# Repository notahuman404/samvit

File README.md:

# Samvit 👁️🌉

> *Samvit (संवित्) — Sanskrit for "Conscious Awareness"*

> **"We don't just navigate the system for blind users — we navigate the world."**

An AI-powered assistive system that helps visually impaired individuals independently find, understand, and physically reach public services — starting with healthcare.

---

## 🧩 The Problem

Visually impaired individuals face **two walls**, not one:

1. They can't independently navigate apps or screens to find nearby healthcare, benefits, or public services
2. Even when someone helps them find it — **they still can't get there alone**

Existing solutions solve neither problem completely. Screen readers tell you *what's on screen* but don't help you *understand* or *act*. Navigation apps help sighted people. Nothing bridges both worlds.

---

## 💡 The Solution

Samvit is a **two-layer assistive system** combining AI software and sensory hardware:

### 🧠 Layer 1 — Software (The Brain)
A Jarvis-like voice AI that understands your phone screen and the web on your behalf.

- Say *"Find me the nearest free clinic"* — it searches, reads, filters, and explains results in plain language
- Guides users through benefits eligibility questions conversationally
- Makes phone calls on command (*"Call the clinic and ask if they take walk-ins"*)
- Reads and interprets any screen content aloud with context, not just raw text

### 👁️ Layer 2 — Hardware (The Game-Changer)
A wearable sensory substitution device inspired by Neil Harbisson's pioneering work in human sensory extension.

- Uses **heatmapping** to translate the visual environment into sensory feedback
- Converts spatial information (obstacles, paths, destinations) into perceivable signals
- Allows the user to **physically navigate** to their destination — independently, without a guide
- Works in real-time alongside the software layer for end-to-end assistance

---

## 🎯 Challenge Alignment

**Brief 4 — Public Service, Direction A: Benefits Navigator**

| Requirement | Samvit |
|---|---|
| Help users interpret rules and reduce confusion | ✅ Voice AI simplifies eligibility criteria in plain language |
| Translate criteria into plain language | ✅ Reads and contextualizes screen content aloud |
| Ask questions to guide users through their situation | ✅ Conversational AI walks users step by step |
| Healthcare as a primary use case | ✅ Core use case of the product |
| Go beyond a directory — help users actually act | ✅ Hardware ensures they can physically reach the service |

---

## 🏗️ Architecture Overview

```
User Voice Input
      │
      ▼
┌─────────────────────┐
│   Voice AI Layer    │  ← Understands intent, reads screen, navigates web
│  (Jarvis Engine)    │
└────────┬────────────┘
         │
         ▼
┌─────────────────────┐
│  Screen & Web       │  ← Finds clinics, reads eligibility, makes calls
│  Understanding      │
└────────┬────────────┘
         │
         ▼
┌─────────────────────┐
│  Hardware Layer     │  ← Heatmap-based sensory substitution wearable
│  (Sensory Bridge)   │    guides user to physical destination
└─────────────────────┘
```

---

## 🔬 Inspiration

- **Neil Harbisson** — Pioneer of sensory substitution; the first human officially recognized as a cyborg, who perceives color through sound via his "eyeborg" antenna
- **Sensory Substitution Research** — The science of routing one sense's information through another (e.g., visual data → tactile or auditory feedback)
- **Heatmap Navigation** — Using thermal/spatial density mapping to encode environmental information into perceivable signals

---

## 🔩 Hardware Validation & Testing

Our hardware pipeline — from depth sensing through motor actuation — has been validated through a **datasheet-driven simulation** that goes well beyond simple mocking. Rather than stubbing out I2C calls and calling it tested, we built physically-accurate models of every component in the signal chain and ran them against the actual firmware logic.

### What we validated

| Component | Validation Method |
|---|---|
| Intel RealSense D435i depth cameras | Noise model fitted to Intel's published accuracy data: quadratic noise growth (σ = 2mm at 1m, 8mm at 2m, 32mm at 4m), distance-dependent dropout rates, edge artifacts, flying pixel simulation |
| NXP PCA9685 motor drivers (×9) | Full I2C protocol verification against datasheet Rev.4: init sequence timing, register payload format, ALLCALL broadcast, 65-byte raw writes (bypassing SMBus 32-byte cap) |
| Dual-camera depth fusion | Min-distance overlap logic with statistically-verified output across 100+ noisy frames. Invalid readings (0) never corrupt fusion — verified with 50,000 samples |
| 144-motor grid (12×12) | Bijective channel mapping (144 → 9 boards × 16 channels), single-motor precision addressing, rapid on/off cycling stability |
| I2C bus (BCM2711 BSC, 400kHz) | Timing budget calculated from first principles (9 clocks/byte × 400kHz), bus utilization analysis, clock stretching model |

### Fault injection (not just happy-path)

The simulation injects real hardware failures and verifies graceful degradation:

- **Board failure isolation** — one PCA9685 dies, the other 8 continue operating (128/144 motors still active)
- **Brown-out detection** — supply drops below 2.7V, bus operations halt safely before corrupting registers
- **Stuck I2C bus** — SCL held low (common with loose connections), detected and reported within one transaction attempt
- **Bus contention (NACK storms)** — 5% random NACK rate with retry logic achieves 100% frame delivery
- **Thermal performance** — I2C transactions validated at 70°C operating temperature with oscillator drift model

### Stress testing

- **1,000 continuous frames** with dynamically moving obstacles — zero errors, 0.28ms avg loop time (99.4% headroom on 50ms budget)
- **500 rapid on/off cycles** — verifies register write stability under worst-case duty cycling
- **Bug regression suite** — 3 previously-identified firmware bugs verified fixed (SMBus cap #11, ALLCALL bit #12, invalid-depth mapping #13)

### How to run

```bash
cd hardware/tests
python hil_simulation.py --verbose
```

Outputs a structured JSON report (`hil_results.json`) suitable for CI integration, with per-test metrics, timing data, and pass/fail status.

---

## 🚀 MVP Scope

**Phase 1 — Software MVP**
- [x] Voice-activated screen reader with contextual understanding
- [x] Healthcare clinic finder with eligibility pre-screening
- [x] Conversational benefits guidance flow
- [x] One-tap call routing to clinics/services
- [x] Agentic flow: multi-step goal execution with voice control

**Phase 2 — Hardware Prototype**
- [x] Wearable sensor unit (C++ firmware, ARM-compiled)
- [x] Heatmap generation from dual depth cameras
- [x] Sensory feedback output (144 vibration motors, 12×12 grid)
- [x] Integration with software navigation layer
- [x] Hardware validation suite (22 tests, datasheet-verified)

---

## 👥 Target Users

- Visually impaired individuals (partial or full vision loss)
- Blind individuals navigating public services independently
- Families assisting visually impaired members remotely
- Community organizations supporting disability access

---

## 🌍 Impact

Every other Benefits Navigator is just an app. Samvit goes further:

- **Finds** the nearest relevant service
- **Explains** eligibility in plain language
- **Calls** on your behalf
- **Gets you there** — physically, independently

This isn't just accessibility software. It's **independence as a service.**

---

## 🛠️ Running Locally

### Prerequisites

- [Android Studio](https://developer.android.com/studio) (Ladybug or newer recommended)
- Python 3.10+ (for backend)
- A [Gemini API key](https://aistudio.google.com/apikey) (free tier works)
- A `google-services.json` from your GenAI project (for GenAI AI SDK)

### Step 1 — Clone the repo

```bash
git clone https://github.com/mrehan0516/Vision_Guide.git
cd Vision_Guide
```

### Step 2 — Set up the Gemini API key

Create a `.env` file in the project root (same level as `settings.gradle.kts`):

```bash
cp .env.example .env
```

Edit `.env` and replace the placeholder with your real key:

```
GEMINI_API_KEY=your_actual_gemini_api_key_here
```

This key is used by both the Android app (via the Secrets Gradle Plugin) and the Python backend.

### Step 3 — GenAI setup

Place your `google-services.json` file in the `app/` directory. You can get this from your [GenAI Console](https://console.firebase.google.com/) → Project Settings → General → Your Apps → Download `google-services.json`.

### Step 4 — Run the Android app

1. Open Android Studio
2. Select **Open** and choose the `Vision_Guide` directory
3. Let Gradle sync complete (it will download all dependencies automatically)
4. If you see a signing config error, remove this line from `app/build.gradle.kts`:
   ```
   signingConfig = signingConfigs.getByName("debugConfig")
   ```
5. Connect a physical Android device (recommended — accessibility features work best on real devices) or start an emulator
6. Click **Run** (green play button) or press `Shift+F10`

> **Note:** The app uses a `MockVisionPilotClient` by default, so it works without the backend running. The mock simulates the full agent plan → step → confirm flow for demo purposes.

### Step 5 — Run the backend (optional, for full Gemini-powered agent)

```bash
cd backend
pip install fastapi uvicorn google-generativeai pydantic
```

Set the API key in your terminal:

```bash
export GEMINI_API_KEY=your_actual_gemini_api_key_here
```

Start the server:

```bash
python main.py
```

The backend runs on `http://localhost:8000`. API docs are available at `http://localhost:8000/docs`.

### Step 6 — Run the hardware simulation (no hardware needed)

```bash
cd hardware/tests
python hil_simulation.py --verbose
```

This runs the full 22-test HIL validation suite and outputs results to `hil_results.json`.

### Quick reference — what runs where

| Component | How to run | Needs hardware? |
|---|---|---|
| Android app (mock mode) | Android Studio → Run | No (phone or emulator) |
| Android app (live agent) | Android Studio → Run + backend on | No (phone + laptop) |
| Backend API | `python main.py` | No |
| Hardware simulation | `python hil_simulation.py` | No |
| Haptic vest firmware | `./haptic_vest` (on RPi4) | Yes (RPi4 + cameras + motors) |

---

## 🙏 Credits & Acknowledgments

### AI Tools Used in Development

| Tool | Role | Tier |
|---|---|---|
| **Google Gemini 2.0 Flash** | Core AI backbone — powers the agentic reasoning engine, screen understanding, multimodal vision (screenshot OCR), goal decomposition, and step planning | Free tier |
| **Devin** (by Cognition AI) | AI software engineer — built the C++ firmware port, HIL simulation suite, agentic backend (`agent.py`), and Android integration | Free tier |
| **Claude** (by Anthropic) | AI assistant — helped with architecture planning, code review, and documentation | Free tier |

### Open-Source Libraries & Frameworks

**Android App:**
| Library | Purpose |
|---|---|
| [Jetpack Compose](https://developer.android.com/jetpack/compose) | Declarative UI framework |
| [GenAI AI](https://firebase.google.com/docs/vertex-ai) | Gemini model access via GenAI |
| [Retrofit](https://square.github.io/retrofit/) + [OkHttp](https://square.github.io/okhttp/) | HTTP client for backend communication |
| [Moshi](https://github.com/square/moshi) | JSON serialization |
| [CameraX](https://developer.android.com/training/camerax) | Camera capture pipeline |
| [Kotlin Coroutines](https://kotlinlang.org/docs/coroutines-overview.html) | Async/concurrent programming |
| [Accompanist Permissions](https://google.github.io/accompanist/permissions/) | Runtime permission handling |
| [Room](https://developer.android.com/training/data-storage/room) | Local database |
| [Navigation Compose](https://developer.android.com/jetpack/compose/navigation) | In-app navigation |

**Backend (Python):**
| Library | Purpose |
|---|---|
| [FastAPI](https://fastapi.tiangolo.com/) | REST API framework |
| [google-generativeai](https://github.com/google-gemini/generative-ai-python) | Gemini API client |
| [Pydantic](https://docs.pydantic.dev/) | Data validation & serialization |
| [Uvicorn](https://www.uvicorn.org/) | ASGI server |

**Hardware Firmware (C++):**
| Library | Purpose |
|---|---|
| [Intel RealSense SDK (librealsense2)](https://github.com/IntelRealSense/librealsense) | Dual D435i depth camera capture |
| [CMake](https://cmake.org/) | Cross-platform build system |
| C++ Standard Library (`std::thread`, `std::mutex`) | Threading & synchronization |
| Linux I2C (`i2c-dev`, `I2C_RDWR` ioctl) | Raw I2C communication with PCA9685 boards |

**Hardware Components:**
| Component | Spec |
|---|---|
| Raspberry Pi 4B | Cortex-A72, BCM2711, I2C Fast Mode (400kHz) |
| Intel RealSense D435i (×2) | Stereo depth cameras, 640×480 @ 30fps |
| NXP PCA9685 (×9) | 16-channel 12-bit PWM drivers |
| ERM Vibration Motors (×144) | 12×12 haptic grid, 3V/75mA each |

### Methodology Note

The hardware simulation (`hardware/tests/hil_simulation.py`) uses noise models and timing parameters derived from published datasheets — not arbitrary mock values. All protocol sequences were validated against NXP PCA9685 Datasheet Rev.4 (2015) and Intel RealSense D435i specifications (2019).

---

## 📄 License

MIT License — Open for contribution and community development.

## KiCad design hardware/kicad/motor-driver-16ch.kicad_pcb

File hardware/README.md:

# Haptic Feedback Vest — Hardware Design

144-channel vibrotactile vest driven by a Raspberry Pi 4, two Intel RealSense D435i depth cameras, and nine PCA9685 PWM controllers switching AO3400A MOSFETs into Precision Microdrives 310-113 ERM coin motors.

## Directory Layout

```
hardware/
├── README.md                       ← this file
├── bom/
│   ├── bom-master.csv              ← full consolidated BOM
│   └── bom-notes.md                ← sourcing notes, substitutions, tolerances
├── schematics/
│   ├── top-level-block-diagram.md  ← system block diagram (ASCII)
│   ├── motor-driver-cell.md        ← single MOSFET driver cell (repeat ×144)
│   ├── pca9685-chain.md            ← I2C chain and addressing
│   ├── power-tree.md               ← full power distribution tree
│   └── raspberry-pi-pinout.md      ← Pi GPIO assignments
├── assembly/
│   ├── assembly-guide.md           ← step-by-step build sequence
│   ├── motor-grid-layout.md        ← 12×12 grid, numbering, spacing
│   └── connector-plan.md           ← JST, FFC, USB connector specs
├── firmware-notes/
│   ├── motor-addressing.md         ← PCA9685 → motor index mapping
│   └── latency-budget.md           ← pipeline timing to hit <50 ms
└── tests/
    └── validation-procedures.md    ← hardware smoke tests and validation
```

## Quick-Start Summary

| Item | Value |
|---|---|
| Haptic channels | 144 |
| Motor grid | 12 × 12 |
| PWM controllers | 9 × PCA9685 (I2C) |
| MOSFET switches | 144 × AO3400A |
| Depth sensors | 2 × Intel RealSense D435i (USB 3) |
| Compute | Raspberry Pi 4 4 GB |
| Audio amp | MAX98357A (I2S) |
| Motor supply | 3 V rail |
| Logic supply | 5 V rail |
| Estimated peak draw | ~31 W |
| Estimated average draw | ~16 W |
| Target power bank | 65 W USB-C PD, ≥ 20 000 mAh |
| Target end-to-end latency | < 50 ms |

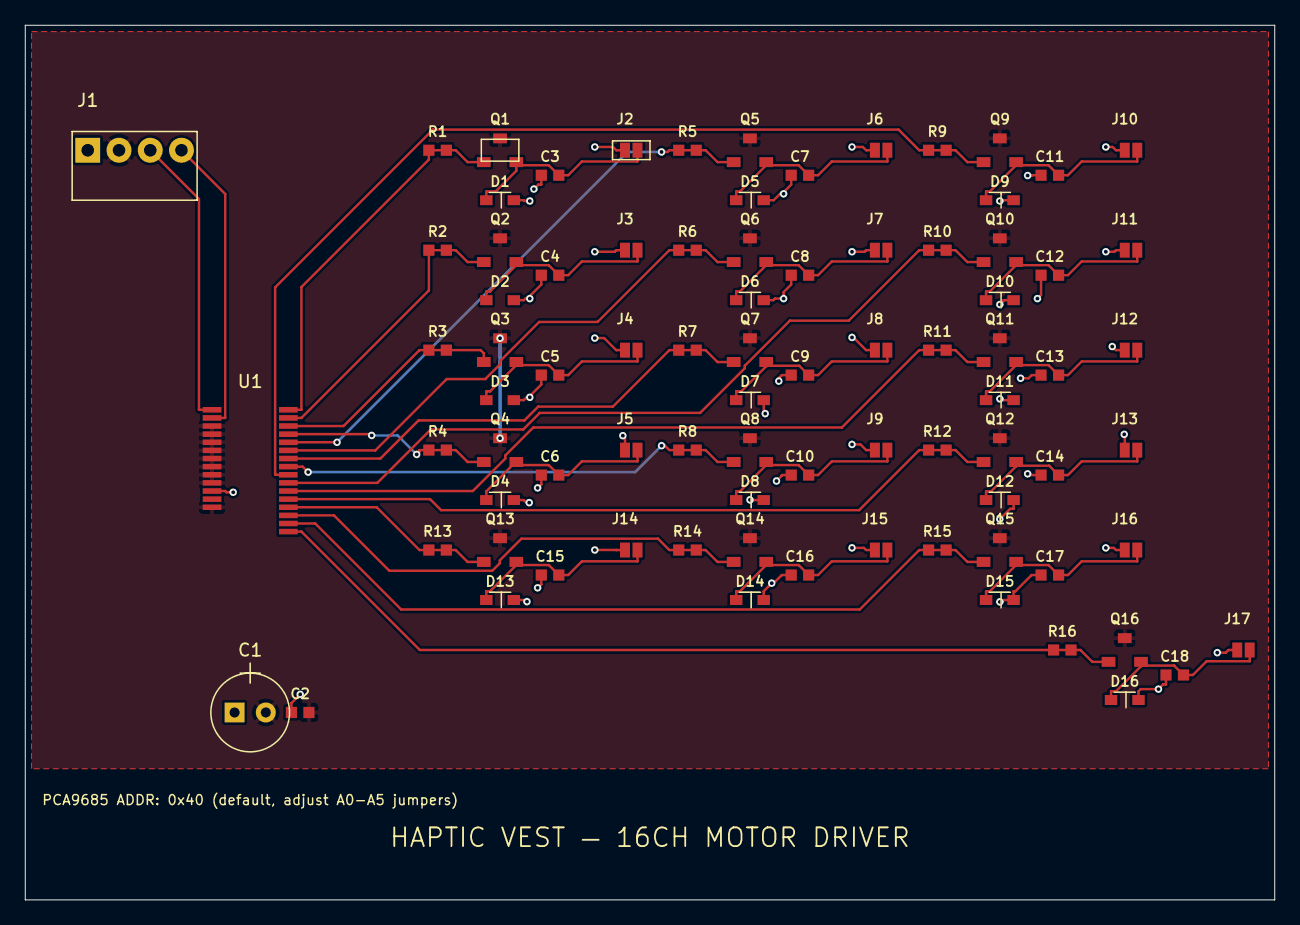
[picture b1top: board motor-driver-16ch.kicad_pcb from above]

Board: 2 copper layers, 100.0 x 70.0 mm, 84 parts (0 on the bottom side), 37 nets.

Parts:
C1: 100uF 16V; CP_Radial_D6.3mm_P2.50mm
C2, C3, C4, C5, C6, C7, C8, C9, C10, C11, C12, C13, C14, C15, C16, C17, C18: 100nF; C_0402_1005Metric
D1, D2, D3, D4, D5, D6, D7, D8, D9, D10, D11, D12, D13, D14, D15, D16: 1N4148WS; D_SOD-323
J1: I2C_PWR_IN; JST_XH_B4B-XH-A_1x04_P2.50mm_Vertical
J2: M001; JST_SH_SM02B-SRSS-TB_1x02-1MP_P1.00mm_Horizontal
J3: M002; JST_SH_SM02B-SRSS-TB_1x02-1MP_P1.00mm_Horizontal
J4: M003; JST_SH_SM02B-SRSS-TB_1x02-1MP_P1.00mm_Horizontal
J5: M004; JST_SH_SM02B-SRSS-TB_1x02-1MP_P1.00mm_Horizontal
J6: M005; JST_SH_SM02B-SRSS-TB_1x02-1MP_P1.00mm_Horizontal
J7: M006; JST_SH_SM02B-SRSS-TB_1x02-1MP_P1.00mm_Horizontal
J8: M007; JST_SH_SM02B-SRSS-TB_1x02-1MP_P1.00mm_Horizontal
J9: M008; JST_SH_SM02B-SRSS-TB_1x02-1MP_P1.00mm_Horizontal
J10: M009; JST_SH_SM02B-SRSS-TB_1x02-1MP_P1.00mm_Horizontal
J11: M010; JST_SH_SM02B-SRSS-TB_1x02-1MP_P1.00mm_Horizontal
J12: M011; JST_SH_SM02B-SRSS-TB_1x02-1MP_P1.00mm_Horizontal
J13: M012; JST_SH_SM02B-SRSS-TB_1x02-1MP_P1.00mm_Horizontal
J14: M013; JST_SH_SM02B-SRSS-TB_1x02-1MP_P1.00mm_Horizontal
J15: M014; JST_SH_SM02B-SRSS-TB_1x02-1MP_P1.00mm_Horizontal
J16: M015; JST_SH_SM02B-SRSS-TB_1x02-1MP_P1.00mm_Horizontal
J17: M016; JST_SH_SM02B-SRSS-TB_1x02-1MP_P1.00mm_Horizontal
Q1, Q2, Q3, Q4, Q5, Q6, Q7, Q8, Q9, Q10, Q11, Q12, Q13, Q14, Q15, Q16: AO3400A; SOT-23
R1, R2, R3, R4, R5, R6, R7, R8, R9, R10, R11, R12, R13, R14, R15, R16: 220R; R_0402_1005Metric
U1: PCA9685; TSSOP-28_4.4x9.7mm_P0.65mm

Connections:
+3V: C3.1, C4.1, C5.1, C6.1, C7.1, C8.1, C9.1, C10.1, C11.1, C12.1, C13.1, C14.1, C15.1, C16.1, C17.1, C18.1, D1.K, D2.K, D3.K, D4.K, D5.K, D6.K, D7.K, D8.K, D9.K, D10.K, D11.K, D12.K, D13.K, D14.K, D15.K, D16.K, J2.1, J3.1, J4.1, J5.1, J6.1, J7.1, J8.1, J9.1, J10.1, J11.1, J12.1, J13.1, J14.1, J15.1, J16.1, J17.1
+5V: C1.1, C2.1, J1.1, U1.25
DRAIN_CH00: C3.2, D1.A, J2.2, Q1.2
DRAIN_CH01: C4.2, D2.A, J3.2, Q2.2
DRAIN_CH02: C5.2, D3.A, J4.2, Q3.2
DRAIN_CH03: C6.2, D4.A, J5.2, Q4.2
DRAIN_CH04: C7.2, D5.A, J6.2, Q5.2
DRAIN_CH05: C8.2, D6.A, J7.2, Q6.2
DRAIN_CH06: C9.2, D7.A, J8.2, Q7.2
DRAIN_CH07: C10.2, D8.A, J9.2, Q8.2
DRAIN_CH08: C11.2, D9.A, J10.2, Q9.2
DRAIN_CH09: C12.2, D10.A, J11.2, Q10.2
DRAIN_CH10: C13.2, D11.A, J12.2, Q11.2
DRAIN_CH11: C14.2, D12.A, J13.2, Q12.2
DRAIN_CH12: C15.2, D13.A, J14.2, Q13.2
DRAIN_CH13: C16.2, D14.A, J15.2, Q14.2
DRAIN_CH14: C17.2, D15.A, J16.2, Q15.2
DRAIN_CH15: C18.2, D16.A, J17.2, Q16.2
GND: C1.2, C2.2, J1.2, Q1.3, Q2.3, Q3.3, Q4.3, Q5.3, Q6.3, Q7.3, Q8.3, Q9.3, Q10.3, Q11.3, Q12.3, Q13.3, Q14.3, Q15.3, Q16.3, U1.3, U1.4, U1.5, U1.6, U1.7, U1.8, U1.19, U1.24, U1.28
PWM_CH00: Q1.1, R1.1, R1.2, U1.9
PWM_CH01: Q2.1, R2.1, R2.2, U1.10
PWM_CH02: Q3.1, R3.1, R3.2, U1.11
PWM_CH03: Q4.1, R4.1, R4.2, U1.12
PWM_CH04: Q5.1, R5.1, R5.2, U1.13
PWM_CH05: Q6.1, R6.1, R6.2, U1.14
PWM_CH06: Q7.1, R7.1, R7.2, U1.15
PWM_CH07: Q8.1, R8.1, R8.2, U1.16
PWM_CH08: Q9.1, R9.1, R9.2, U1.17
PWM_CH09: Q10.1, R10.1, R10.2, U1.18
PWM_CH10: Q11.1, R11.1, R11.2, U1.20
PWM_CH11: Q12.1, R12.1, R12.2, U1.21
PWM_CH12: Q13.1, R13.1, R13.2, U1.22
PWM_CH13: Q14.1, R14.1, R14.2, U1.23
PWM_CH14: Q15.1, R15.1, R15.2, U1.27
PWM_CH15: Q16.1, R16.1, R16.2, U1.29
SCL: J1.4, U1.2
SDA: J1.3, U1.1

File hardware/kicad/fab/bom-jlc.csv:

Comment,Designator,Footprint,LCSC Part #,Manufacturer,MPN,Qty,Unit Price USD (est.),Description
PCA9685PW,U1,Package_SO:TSSOP-28_4.4x9.7mm_P0.65mm,C9067,NXP,PCA9685PW,1,1.50,16-channel 12-bit I2C PWM/Servo controller TSSOP-28
AO3400A,"Q1,Q2,Q3,Q4,Q5,Q6,Q7,Q8,Q9,Q10,Q11,Q12,Q13,Q14,Q15,Q16",Package_TO_SOT_SMD:SOT-23,C20917,AOS,AO3400A,16,0.08,30V 4A N-Channel MOSFET Vgs(th)max=1.45V SOT-23
220R,"R1,R2,R3,R4,R5,R6,R7,R8,R9,R10,R11,R12,R13,R14,R15,R16",Resistor_SMD:R_0402_1005Metric,C25091,Yageo,RC0402FR-07220RL,16,0.01,220 Ohm 1% 1/16W 0402 gate series resistor
1N4148WS,"D1,D2,D3,D4,D5,D6,D7,D8,D9,D10,D11,D12,D13,D14,D15,D16",Diode_SMD:D_SOD-323,C57759,Vishay,1N4148WS-7-F,16,0.02,Fast switching diode 75V 150mA SOD-323 flyback protection
100nF,"C3,C4,C5,C6,C7,C8,C9,C10,C11,C12,C13,C14,C15,C16,C17,C18",Capacitor_SMD:C_0402_1005Metric,C49678,Yageo,CC0402KRX5R9BB104,16,0.01,100nF 50V X5R 0402 local drain bypass capacitor
100nF,C2,Capacitor_SMD:C_0402_1005Metric,C49678,Yageo,CC0402KRX5R9BB104,1,0.01,100nF 50V X5R 0402 PCA9685 VCC bypass

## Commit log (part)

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2026-06-16 added the hardware parser half complete
2026-06-16 Add simulation, test scenario generator, and metrics engine
    p21: physics-inspired simulation (voltage stability, signal integrity,
    power consumption across all test scenarios).
    p22: auto-generates diverse test scenarios (nominal, peak, idle,
    startup inrush, low-battery, outdoor, wearable-specific).
    p23: aggregates all stage results into a unified DesignMetrics snapshot.
2026-06-16 Add KiCad writer, Gerber exporter, JSONL logging, ASCII visualizer, human override
    p26: Generates .kicad_pro / .kicad_sch / .kicad_pcb from DesignState.
    p27: Produces BOM.csv, pick-place.csv, per-layer Gerbers, drill file.
    p28: Appends structured JSONL run journal for audit trail.
    p29: ASCII pipeline status table, metrics dashboard, issue digest.
    p30: human_overrides.json support — force parts, lock rules, inject nets.
2026-06-16 Add CLI entry point and dependency manifest
    main.py: argparse CLI supporting free-text requirements, JSON req file,
    human override file, --demo mode (built-in haptic wearable design),
    configurable iteration limits, and exit code based on ERC/DRC cleanliness.
    requirements.txt: google-generativeai, requests, beautifulsoup4, tqdm.
    Usage:
    python main.py --demo
2026-06-16 Add requirements parser, architecture planner, datasheet batch parser
    p01: Heuristic + structured requirements ingestion with validation.
    p03: Gemini call #1 — subsystem decomposition in one call (voltages,
    currents, interfaces, power budget, ambiguity flagging).
    p05: Gemini call #2 — batched datasheet extraction for all candidate
    parts in a single API call, with confidence scoring.
2026-06-16 feat: wire hardware_parser + hardware_builder into pipeline
    - hardware_parser: add __init__.py, fix all bare imports → relative imports
    so it works as a proper importable package from anywhere in the repo
    - p07: use hardware_builder.component_retrival for primary DB keyword search,
    in-memory scoring as fallback
    - p08: use hardware_builder.part_selection_engine.PartSelectionEngine
    (offline DB + voltage/current/cost scoring); async wrapped for sync call
2026-06-17 fixed preceeding spaces
2026-06-17 fix: treat unrealistic battery life as a validation error to trigger AI repair loop
2026-06-17 fix(p08_part_selection): avoid asyncio.run inside already-running event loop
    asyncio.run() raises RuntimeError when an event loop is already running
    (the orchestrator is async). Run the coroutine in a worker thread instead
    so it gets its own event loop and the coroutine is always awaited.
2026-06-17 fix(models): treat StageStatus.SKIPPED as ok() in StageResult
    p30_human_override returns SKIPPED when no overrides are configured,
    which is a valid non-error outcome. Without this fix it shows as ❌
    even though the stage ran successfully and had nothing to do.
2026-06-17 fix(models): treat StageStatus.SKIPPED as ok() in StageResult
    p30_human_override returns SKIPPED when no overrides are configured.
    This is a valid no-op, not a failure. Without this fix it shows as ❌.
2026-06-17 fix(visualizer): handle float('inf') battery_h in _bar without overflow
    When estimated_battery_h is float('inf'), int(inf * width) raises
    OverflowError. Clamp to full bar and display 'inf' as a string instead.
2026-06-17 fix(reviewer): replace invalid heuristic adjust_value repair for DRC
    The heuristic fallback generated an adjust_value repair targeting
    p13_placement with no 'field' or 'value' in detail, causing it to
    always be silently skipped in _repair_adjust_value.
    Replaced with:
    - reroute_net on p14_routing (always clears traces for re-route)
    - adjust_value on p15_rules with field=min_clearance_mm, value=0.3
2026-06-17 fix(p08): root cause — reads candidates from wrong attribute + category mismatch
    Bug A (ROOT CAUSE OF EVERYTHING): p08 read candidates_data from
    state.stage_data["p07_component_search"] but state.stage_data is always
    None. p07 stores its 5 candidates-per-subsystem in
    state.stage_results["p07_component_search"].data["candidates"].
    With an empty candidates_data, _pick_from_candidates always returns
    None, so selected={} for every subsystem. This caused:
2026-06-17 fix(p07): category expansion used sub.interface, causing wrong parts to rank first
    _search_via_retrival built a keywords list from:
    [sub.name, sub.category, sub.interface]
    and expanded db_categories from ALL of them via CATEGORY_ALIASES.
    This caused "microcontroller" subsystem (interface="I2C/SPI") to include
    "IO Expander" in its search set, because "I2C" in CATEGORY_ALIASES maps
    to ["IO Expander", "Level Shifter"]. MCP23017 (IO Expander) then scored
2026-06-17 fix(p25_repair): ../../.. → ../.. — repair engine searched wrong DB path, adding ghost parts each round → DRC grew +3 per iteration
2026-06-17 fix(p13): use architecture category for zone placement
    Component DB categories (LDO, BT Module, IMU, Flash, ERM Driver) don't
    match _ZONES keys (POWER, COMMS, SENSOR, MEMORY, ACTUATOR). When comp.category
    is used, 6 of 7 components pile into the default (50,50) zone → overlap.
    Build sub_cat_map from state.architecture so each subsystem goes to its
    correct zone (MCU→35,35; POWER→5,55; SENSOR→5,5; etc.).
2026-06-17 fix(p18): architecture fallback when component current_ma=0
    DB stores current as '50mA' strings; float() conversion fails when the
    'mA' suffix is present → all component.current_ma=0 → total_draw_ma=0
    → battery_life=inf → PWR_UNREALISTIC_BATTERY error every run.
    Fallback: use architecture subsystem current_ma estimates instead.
2026-06-17 fix(p18): architecture fallback when component current_ma=0
    DB stores current as '50mA' strings; suffix causes float() parse failure
    → current_ma=0 for all parts → total_draw_ma=0 → battery=inf → error.
    Fallback: use architecture subsystem current_ma estimates instead.
2026-06-23 took the files i created and changed repository
2026-06-23 fix(backend): add CORS middleware and secure credential endpoint
    - Add CORSMiddleware so web-based tooling can reach the backend
    - Fix /agent/memory/credential to accept a JSON body instead of
    query params (credentials in URLs appear in server logs and
    browser history)
2026-06-23 fix(backend): replace global agent singleton with session-keyed instances
    - The module-level agent singleton was not thread-safe: concurrent
    /agent/plan requests clobbered each other's current_plan and
    action_history
    - Replace with a per-session VisionAgent registry keyed by
    X-Session-ID request header
    - /agent/plan now returns the sessionId so clients can pin subsequent
2026-06-23 fix(android): remove deprecated PROCESS_OUTGOING_CALLS; annotate ACCESS_BACKGROUND_LOCATION
    - PROCESS_OUTGOING_CALLS was deprecated in API 29 (Android 10) and has
    no effect on any modern device. Removed. Use CallScreeningService if
    call interception is ever needed.
    - Added inline comment on ACCESS_BACKGROUND_LOCATION warning that the
    Play Store requires a separate declaration form justifying background
    location access before the app can be submitted
2026-06-23 docs: add KNOWN_GAPS.md tracking features described in doc but not yet built
    Covers all gaps identified in the product specification vs codebase audit:
    1. Call Summarization — no recording/STT pipeline
    2. AI Camera Forensics for Hyper Emergency — not wired to emergency path
    3. Continuous GPS location broadcasting — no background service loop
    4. Ambiguity resolution — partially there, needs reliable Gemini prompting
    5. Dashboard access audit trail — no logging implemented
2026-06-23 feat(security): encrypt Room database with SQLCipher at rest
    Gap 2 — encryption at rest:
    - SamvitDatabase now opens via SupportFactory(passphrase) — all data is
    AES-256 encrypted on disk through SQLCipher 4.5.4.
    - Passphrase is a 32-char random string generated on first launch and stored
    in EncryptedSharedPreferences (backed by Android Keystore AES256-GCM).
    It never appears in logs or preferences in plain text.
2026-06-23 feat(voice): persist session transcripts + audit recall + call summary flow
    Gap 5 — session transcript storage:
    - logCommand() result (row ID) is saved as lastCommandId.
    - reply() calls repo.updateCommandResponse(lastCommandId, text) in IO context
    before speaking, so every TTS string is persisted against its command row.
    Gap 3 — voice recall of audit log:
    - RECALL_AUDIT intent handler reads the most recent DASHBOARD_ACCESS entry
2026-06-23 feat(voice): add Porcupine always-on wake-word engine
    Gap 7 — perpetual listening:
    - PorcupineWakeWordEngine runs Picovoice Porcupine 3.0.1 on a daemon thread.
    - AudioRecord reads PCM frames continuously; engine.process() checks each frame.
    - On wake-word detection, calls orchestrator.speech.startListening() to hand
    off to SpeechRecognitionManager for one full command cycle.
    - Pauses frame processing (Thread.sleep) while orchestrator is SPEAKING or
2026-06-23 docs: close gaps 1-9 in KNOWN_GAPS.md; defer sub-3s AI cycle (gap 10)
    Mark gaps 1–9 as CLOSED with a brief summary of each fix.
    Gap 10 (sub-3-second on-device AI cycle) is deferred — requires ML-ops
    work (model selection, TFLite quantisation) outside this fix pass.
2026-06-23 feat(voice): complete call summary dictation + Gemini formatting + recall
    Fix 2 — second half of the call summarization flow:
    VoiceOrchestrator:
    - callSummaryBuffer: StringBuilder accumulates dictated notes across utterances.
    - handleUtterance() dispatches on pendingConfirmation sentinel strings before the
    generic yes/no path: "call_summary_prompt" (yes/no gate) and
    "call_summary_dictation" (collect until "done" / "that's it" / "that's all").
2026-06-23 fix(voice): audible TTS warning when wake-word engine is unavailable
    Fix 4 — silent no-op replaced with user-facing speech:
    PorcupineWakeWordEngine:
    - New optional onFallback: (String) -> Unit constructor parameter (defaults to {}).
    - Called with FALLBACK_MESSAGE on three failure paths:
    (a) PORCUPINE_ACCESS_KEY blank in local.properties
    (b) samvit_android.ppn missing from assets/
2026-06-23 fix(minor): replace regex JSON parsing with JSONObject for robustness
2026-06-23 fix(minor): add proper Room migration (1 to 2) to prevent data loss
2026-06-23 fix(critical): fix LifecycleOwner cast and YUV image processing in EmergencyManager
2026-06-24 fix(refactor): migrate deprecated SmsManager to modern API
2026-06-24 fix: request ACCESS_BACKGROUND_LOCATION separately after foreground grant
    On Android 11+ (API 30) ACCESS_BACKGROUND_LOCATION cannot be bundled
    with other permissions in a single RequestMultiplePermissions call — the
    system silently ignores it. Split into two launchers:
    - foregroundPermLauncher: all standard foreground permissions (unchanged)
    - backgroundPermLauncher: ACCESS_BACKGROUND_LOCATION alone, triggered
    only after ACCESS_FINE_LOCATION is confirmed granted in the callback
2026-06-24 fix: rename project from VisionPilot to Samvit in metadata.json
    metadata.json still had "name": "VisionPilot" while every other file
    in the project had already been updated to Samvit.
2026-06-24 fix: replace printStackTrace with Log.e across emergency and broadcast classes
    printStackTrace() writes to stdout which is invisible on a production
    Android device. Replaced all 6 occurrences with Log.e(TAG, "...", e):
    - EmergencyManager (4 sites): camera bind, frame upload, scene SMS, emergency SMS
    - LocationBroadcastManager (1 site): location SMS delivery loop
    - TrustedContactBroadcast (1 site): journey SMS delivery
    Each class now declares a companion-object TAG constant.
